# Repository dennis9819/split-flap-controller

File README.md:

# 3D Printable split flap display

Welcome to **split-flap-controller**, the firmware + hardware design for driving a modular, scalable split-flap display system.

Development of this project began in 2024 with the goal of creating a robust, DIY split-flap display that anyone can build and customize themselves. Inspired by the iconic Frankfurt Airport display, this project aims to recreate the nostalgic mechanical aesthetic and characteristic flipping sound that made those displays so memorable.

__Ongoing Project! This repository is not final.__

## Project goals
- **Modularity** – Each flap module is independent and addressable, allowing for scalable display sizes.  
- **DIY-Friendly Design** – Open schematics, PCBs, and firmware make it accessible for makers and hobbyists.  
- **Robust Firmware** – Written in C, with features like error handling, EEPROM-stored calibration, and motor homing logic.  
- **Authentic Aesthetic** – Recreates the distinctive motion and sound of traditional airport-style displays.  
- **Modern Communication** – Supports RS-485 half-duplex at 57600 baud with WebSocket integration for control from a host system.  
- **Open for Extension** – Designed to support other MCUs, motor drivers, or mechanical formats.

## Features

### Hardware
- SMD-based controller board (Atmega8 MCU)  
- Modular RS-485 communication chain 
- Integrated motor driver and position sensor handling
- Modules connect to a single backplane
- Hall-effect sensor homing
- Robust error handling
  - detects homing faults, stuck drums, overcurrent and bus errors
  - activates a failSafe condition on critical fault
  - can be reset via RS485 in most conditions
  - checks validity of each packet via checksum

### Firmware
- Lightweight communication protocol with checksum and addressing  
- Fault detection (homing failure, overcurrent, invalid position)  
- Persistent settings stored in EEPROM  
- CRC check of each message

### Software
- WebSocket-based control server  
- Modular architecture for future GUI or API integrations  
- Easily portable to other platforms and MCUs
- Nginx Webserver allows you to controll the display with your smartphone
- very fast and written in plan c. I'm using libjson and libws for JSON handling and the WebSocket server

## CAD
This display is designed in **Fusion360**. All schematics and boards are designed in **KiCAD 9**.

Most parts can be 3d printed. The modular backpanel needs to be fabricated from sheetmetal. You can use suppliers like JLCPCB for manufacturing or design a different 3d printable solution.

If you want to generate custom flaps, you can find my flap generator here: [split-flap-generator](https://github.com/dennis9819/split-flap-generator)

## License

This project is open source and available under the [AGPL-3.0 License](LICENSE).

## Documentation
- [SFBus Protocol](software/pc_client/doc/sfbus-proto.md)
- [Websockets Protocol](software/pc_client/doc/api-doc.md)
- [BOM](cad/BOM_FlapUnit.md)
- Build guide wil follow soon!

## Power Consumption
Each Module pulls arround 110mA. This is roughly 1.4W of power. 
This can be reduced by turning off the motors in idle. 

---
## Credits
This is a 3D printable, expandable split flap display based on the original design of [David Königsmann](https://github.com/davidkingsman/split-flap).
This version uses his drum and flap design but completly redesigns the rest of the system.

The firmware as well as the Server is completly rewritten from scratch.

Feel free to checkout his more affordable and diy friendly design.

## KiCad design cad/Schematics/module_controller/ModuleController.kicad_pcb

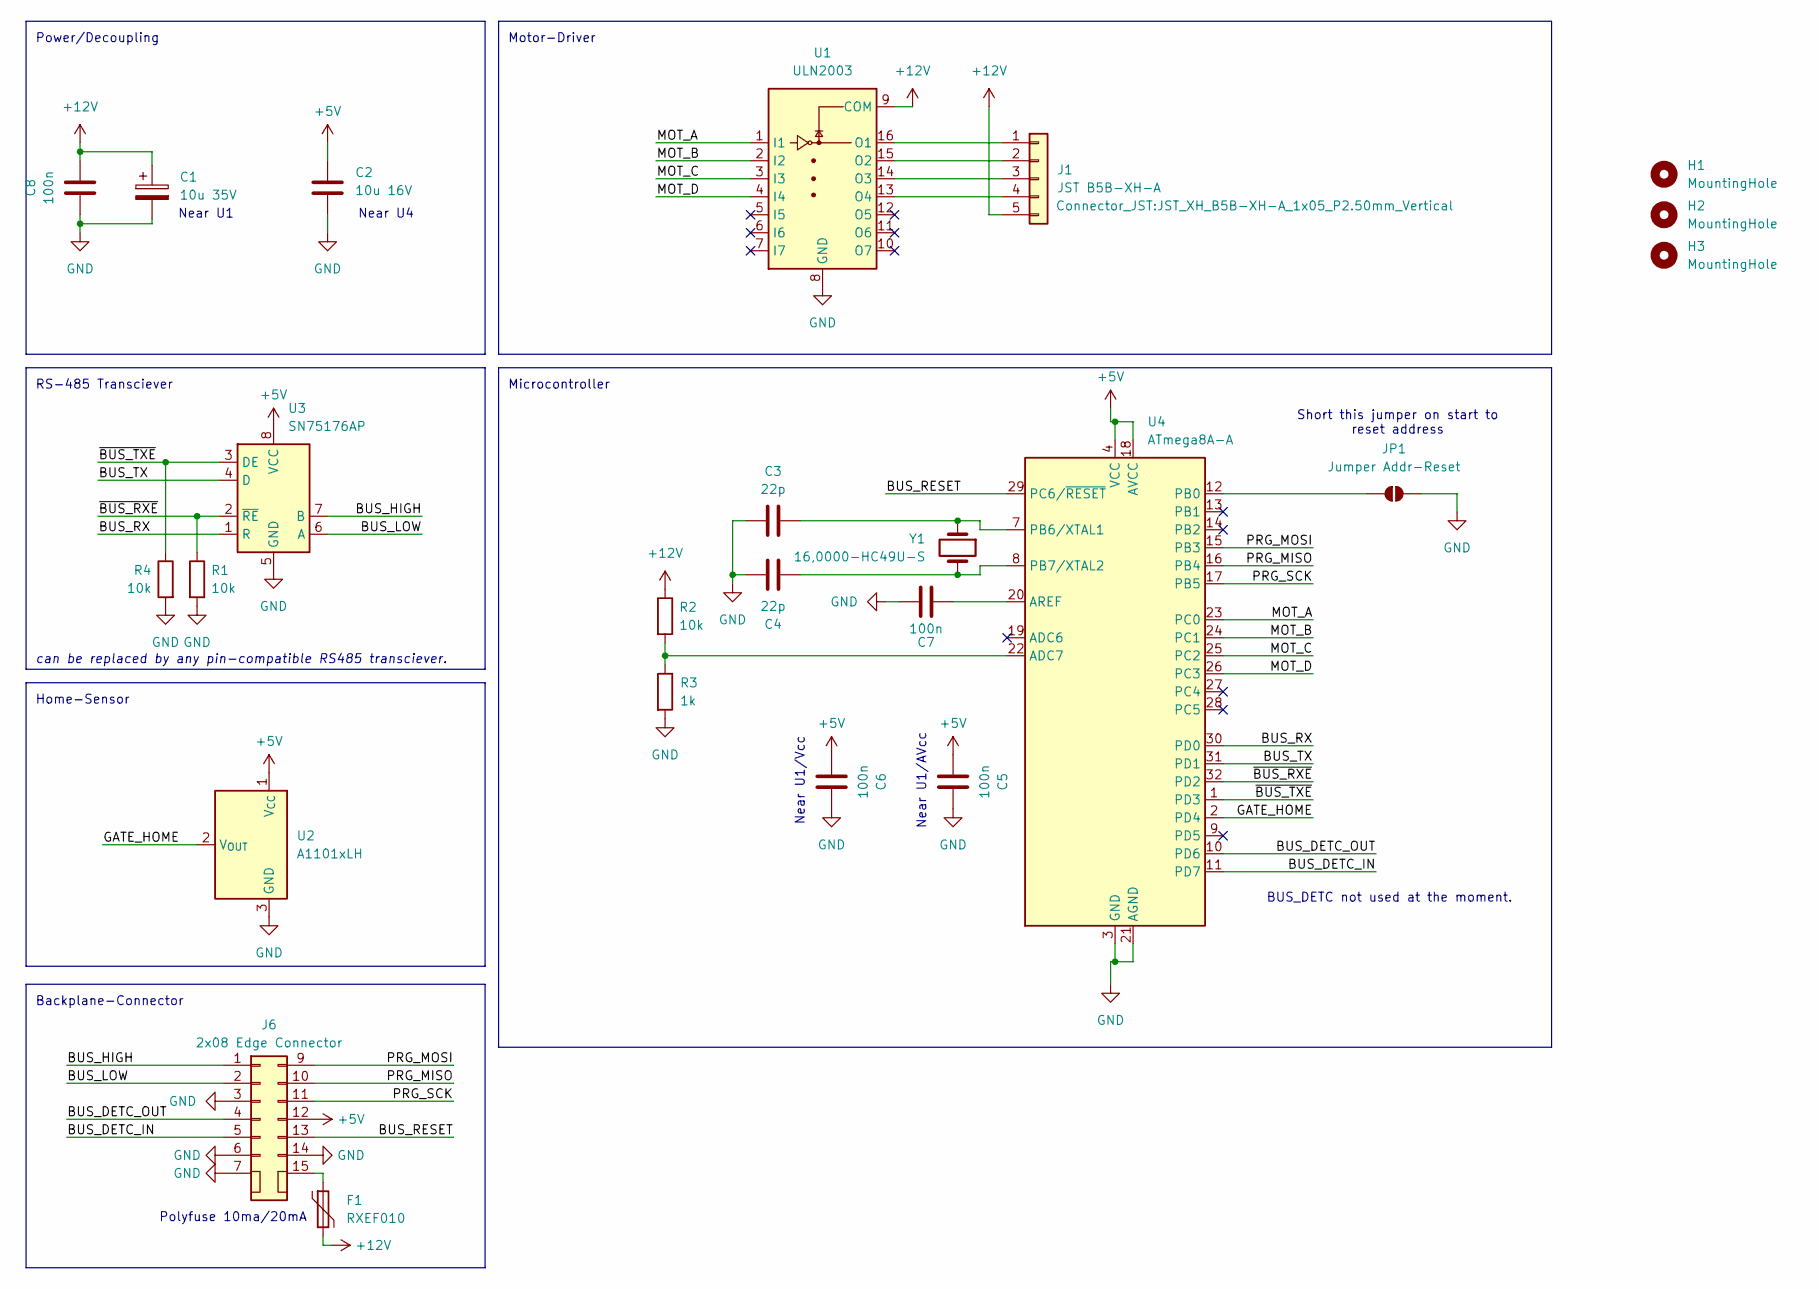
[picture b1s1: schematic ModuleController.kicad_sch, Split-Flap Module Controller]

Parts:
C1: 10u 35V; CP_Radial_D6.3mm_P2.50mm
C2: 10u 16V; C_1206_3216Metric
C3, C4: 22p; C_0805_2012Metric
C5, C6, C7, C8: 100n; C_0805_2012Metric
F1: RXEF010; Fuse_0805_2012Metric
H1, H2, H3: MountingHole; MountingHole_3.2mm_M3_DIN965_Pad
J1: JST B5B-XH-A; JST_XH_B5B-XH-A_1x05_P2.50mm_Vertical
J6: 2x08 Edge Connector; Card Edge 16 power
JP1: Jumper Addr-Reset; SolderJumper-2_P1.3mm_Open_Pad1.0x1.5mm
R1, R2, R4: 10k; R_0805_2012Metric
R3: 1k; R_0805_2012Metric
U1: ULN2003; DIP-16_W7.62mm
U2: A1101xLH; SOT-23W
U3: SN75176AP; DIP-8_W7.62mm
U4: ATmega8A-A; TQFP-32_7x7mm_P0.8mm
Y1: 16,0000-HC49U-S; Crystal_HC49-U_Vertical

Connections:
+5V: C2.1, C5.2, C6.2, J6.12, U2.1 (V_{CC}), U3.8 (VCC), U4.4 (VCC), U4.6 (VCC), U4.18 (AVCC)
+12V: C1.1, C8.1, F1.2, J1.5, R2.1, U1.9 (COM)
/BUS_DETC_IN: J6.5, U4.11 (PD7)
/BUS_DETC_OUT: J6.4, U4.10 (PD6)
/BUS_HIGH: J6.1, U3.7 (B)
/BUS_LOW: J6.2, U3.6 (A)
/BUS_RESET: J6.13, U4.29 (PC6/~RESET)
/BUS_RX: U3.1 (R), U4.30 (PD0)
/BUS_TX: U3.4 (D), U4.31 (PD1)
/GATE_HOME: U2.2 (V_{OUT}), U4.2 (PD4)
/MOT_A: U1.1 (I1), U4.23 (PC0)
/MOT_B: U1.2 (I2), U4.24 (PC1)
/MOT_C: U1.3 (I3), U4.25 (PC2)
/MOT_D: U1.4 (I4), U4.26 (PC3)
/PRG_MISO: J6.10, U4.16 (PB4)
/PRG_MOSI: J6.9, U4.15 (PB3)
/PRG_SCK: J6.11, U4.17 (PB5)
/~BUS_RXE: R1.1, U3.2 (~RE), U4.32 (PD2)
/~BUS_TXE: R4.1, U3.3 (DE), U4.1 (PD3)
GND: C1.2, C2.2, C3.1, C4.1, C5.1, C6.1, C7.1, C8.2, J6.3, J6.6, J6.7, J6.14, JP1.2 (B), R1.2, R3.2, R4.2, U1.8 (GND), U2.3 (GND), U3.5 (GND), U4.3 (GND), U4.5 (GND), U4.21 (AGND)
unnamed: J1.1, U1.16 (O1)
unnamed: J1.2, U1.15 (O2)
unnamed: J1.3, U1.14 (O3)
unnamed: J1.4, U1.13 (O4)
unnamed: F1.1, J6.15
unnamed: JP1.1 (A), U4.12 (PB0)
unnamed: R2.2, R3.1, U4.22 (ADC7)
unnamed: C7.2, U4.20 (AREF)
unnamed: C3.2, U4.7 (PB6/XTAL1), Y1.1
unnamed: C4.2, U4.8 (PB7/XTAL2), Y1.2

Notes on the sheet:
Motor-Driver
RS-485 Transciever
Power/Decoupling
Polyfuse 10ma/20mA
Home-Sensor
Short this jumper on start to reset address
Backplane-Connector
BUS_DETC not used at the moment.
Near U1
can be replaced by any pin-compatible RS485 transciever.
Near U1/AVcc
Near U1/Vcc
Microcontroller
Near U4

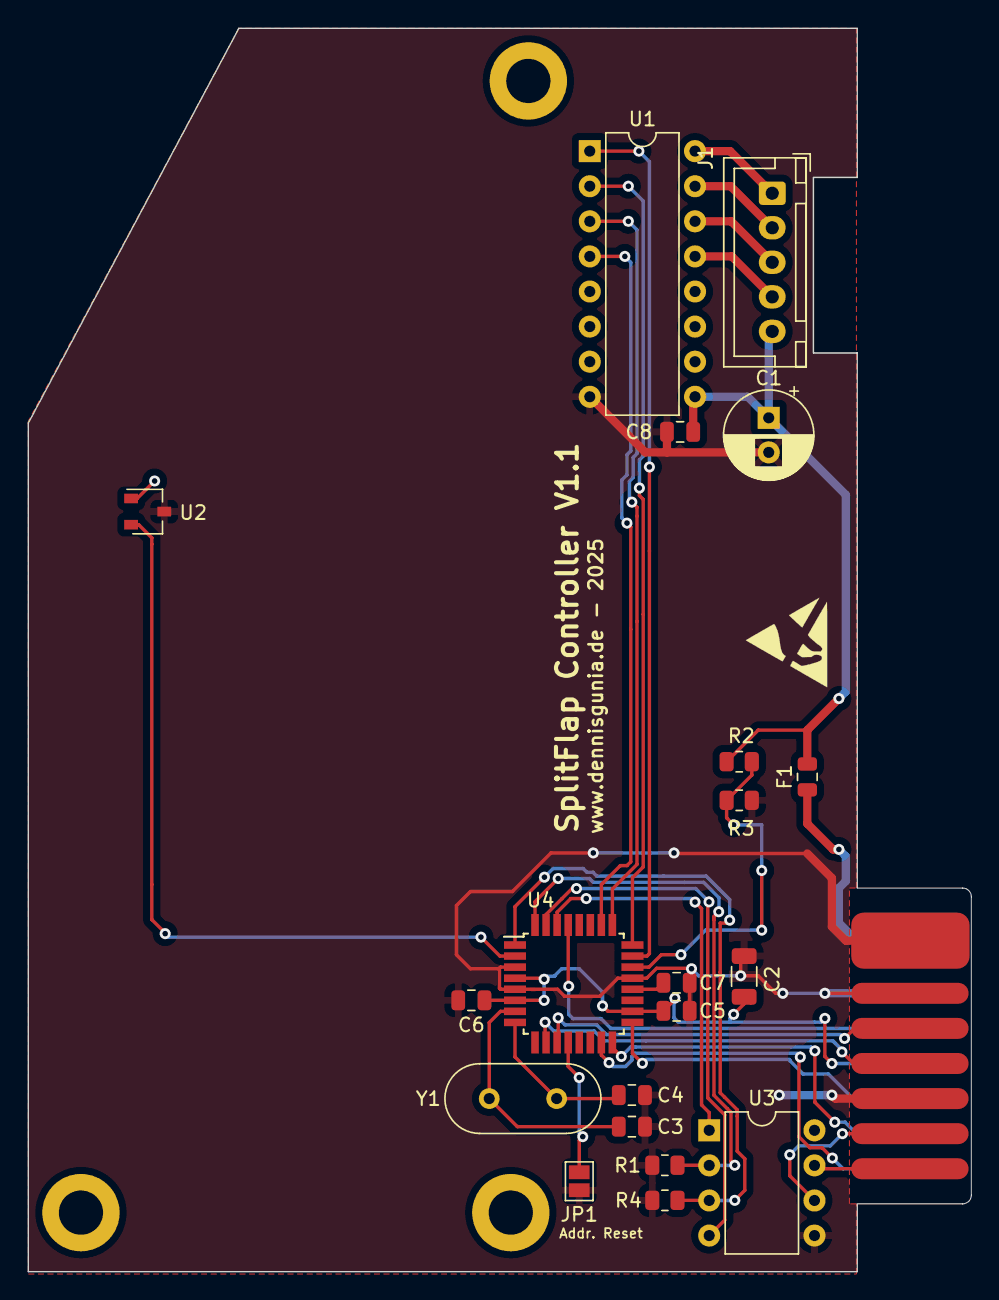
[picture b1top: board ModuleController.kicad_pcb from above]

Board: 2 copper layers, 68.3 x 90.0 mm, 24 parts (0 on the bottom side), 30 nets.

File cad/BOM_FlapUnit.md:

# Bill of Material for 1U/2U Flap Unit

## 3D Printed Parts 
| part-number | part | file | amount | notes |
| ----------- | ---- | ---- | ------ | ----- |
| FU-001 | Unit Frame Base     | STL Unit/splitflap-unit-base.stl | 1 | common for all units |
| FU-002 | Unit Frame Cover 1U | STL Unit/splitflap-cover-1u.stl  | 1 | only for 1U wide unit|
| FU-003 | Unit Frame Cover 2U | STL Unit/splitflap-cover-2u.stl  | 1 | only for 2U wide unit|
| FU-004 | Unit Drum Core      | STL Unit/splitflap-drum-core.stl | 1 | common for all units |
| FU-005 | Unit Drum Core 1U   | STL Unit/splitflap-drum-outer-1u.stl | 1 | only for 1U wide unit|
| FU-006 | Unit Drum Core 2U   | STL Unit/splitflap-drum-outer-2u.stl | 1 | only for 2U wide unit|
| FU-007 | Flaps   | ... | 45 | |
- 49 Individual Parts per module

## Hardware

| part-number | part | amount | notes |
| ----------- | ---- | ------ | ----- |
| FU-011      | Ball Bearing 684ZZ (9 x 4 x 4mm) | 1 | |
| FU-012      | Stepper 28BYJ-48 DC 12V | 1 |  **!! Use 12V Variant. NOT 5V !!**|
| FU-013      | Heat insert M3 x 3mm | 3 | |
| FU-014      | Heat insert M3 x 5mm | 4 | |
| FU-015      | M3x5 Screw DIN 912 | 3 | |
| FU-016      | M3x12 Screw DIN 912 | 2 | |
| FU-017      | M3x8 Screw DIN EN ISO 10642 | 2 | |
| FU-018      | Magnet round d=2mm | 1 | |
- 17 Individual Parts per module

## Electronics
| part-number | part | amount | notes |
| ----------- | ---- | ------ | ----- |
| FU-031      | Module Controller PCB | 1 | |
| FU-032      | ATmega8A-A | 1 | |
| FU-033      | SN75176AP | 1 | |
| FU-034      | ULN2003 | 1 | Can be salvaged from the driver board that usually comes with the stepper motor |
| FU-035      | A1101xLH | 1 | SOT-23W variant! |
| FU-036      | 16,0000-HC49U-S Crystal | 1 |  |
| FU-037      | Capacitor 10u 35V (Radial_D6.3mm_P2.50mm) | 1 |  |
| FU-038      | Capacitor 10u 16V (1206) | 1 |  |
| FU-039      | Capacitor 22p (0805) | 2 |  |
| FU-040      | Capacitor 100n (0805) | 4 |  |
| FU-041      | Fuse 200mA (0805) | 1 |  |
| FU-042      | JST B5B-XH-A | 1 |  |
| FU-043      | Resistor 1k | 1 |  |
| FU-044      | Resistor 10k | 3 |  |
- 20 Individual Parts per module


## Summary:
Parts per module: 76 (mostly 3d printed)

# Bill of Material for 4Unit Backplane

## 3D Printed Parts 
| part-number | part | file | amount | notes |
| ----------- | ---- | ---- | ------ | ----- |
| FP-001      | Upper Slot | STL Slot/splitflap-slot-upper.stl | 1 |  |
| FP-002      | Lower Slot | STL Slot/splitflap-slot-lower.stl | 1 |  |
- 2 Individual Parts per module

## Sheet metal
| part-number | part | file | amount | notes |
| ----------- | ---- | ---- | ------ | ----- |
| FP-003      | Backplane | Sheet Metal/sheet-metal-backplate.dxf | 1 |  |
- 1 Individual Parts per module

## Hardware
| part-number | part | amount | notes |
| ----------- | ---- | ------ | ----- |
| FP-011      | Heat insert M4 x 5mm | 4 | |
| FP-012      | Heat insert M3 x 5mm | 4 | |
| FP-013      | M3x5 Screw DIN 912 | 8 | |
| FP-014      | M4x10 Screw DIN 912 | 4 | |
| FP-015      | M3x5 Standoff | 8 | |
| FP-016      | M3 Nut | 4 | |
- 32 Individual Parts per module

## Electronics
| part-number | part | amount | notes |
| ----------- | ---- | ------ | ----- |
| FU-031      | Backplane PCB | 1 | |
| FU-032      | PhoenixContact_MSTBA_2,5_2-G-5,08 | 2 | |
| FU-033      | Phoenix_MSTB:PhoenixContact_MSTBA_2,5_3-G-5,08 | 4 | |
| FU-034      | L7805 | 1 |  |
| FU-035      | 74AHCT1G125 | 1 | |
| FU-036      | 2x08 Edge Connector | 4 |  |
- 13 Individual Parts per module

## Summary:
Parts per assembly: 48 

# Bill of Material for Backplane connection bracket
## Sheet metal
| part-number | part | file | amount | notes |
| ----------- | ---- | ---- | ------ | ----- |
| FC-001      | Bracket | sheet-metal-connector-middle.dxf | 1 |  |
- 1 Individual Parts per module

## Hardware
| part-number | part | amount | notes |
| ----------- | ---- | ------ | ----- |
| FC-011      | M4x10 | 8 | |
| FC-012      | M4 Nut | 8 | |
- 16 Individual Parts per module

## Summary:
Parts per assembly: 17 

# Parts for full display (12x3)
- Display Units: 36 (2736 Parts)
- Backplane Units: 9 (432 Parts)
- Backplane Connectors: 12 (204 Parts)
- Sum: 3372 Individual Parts

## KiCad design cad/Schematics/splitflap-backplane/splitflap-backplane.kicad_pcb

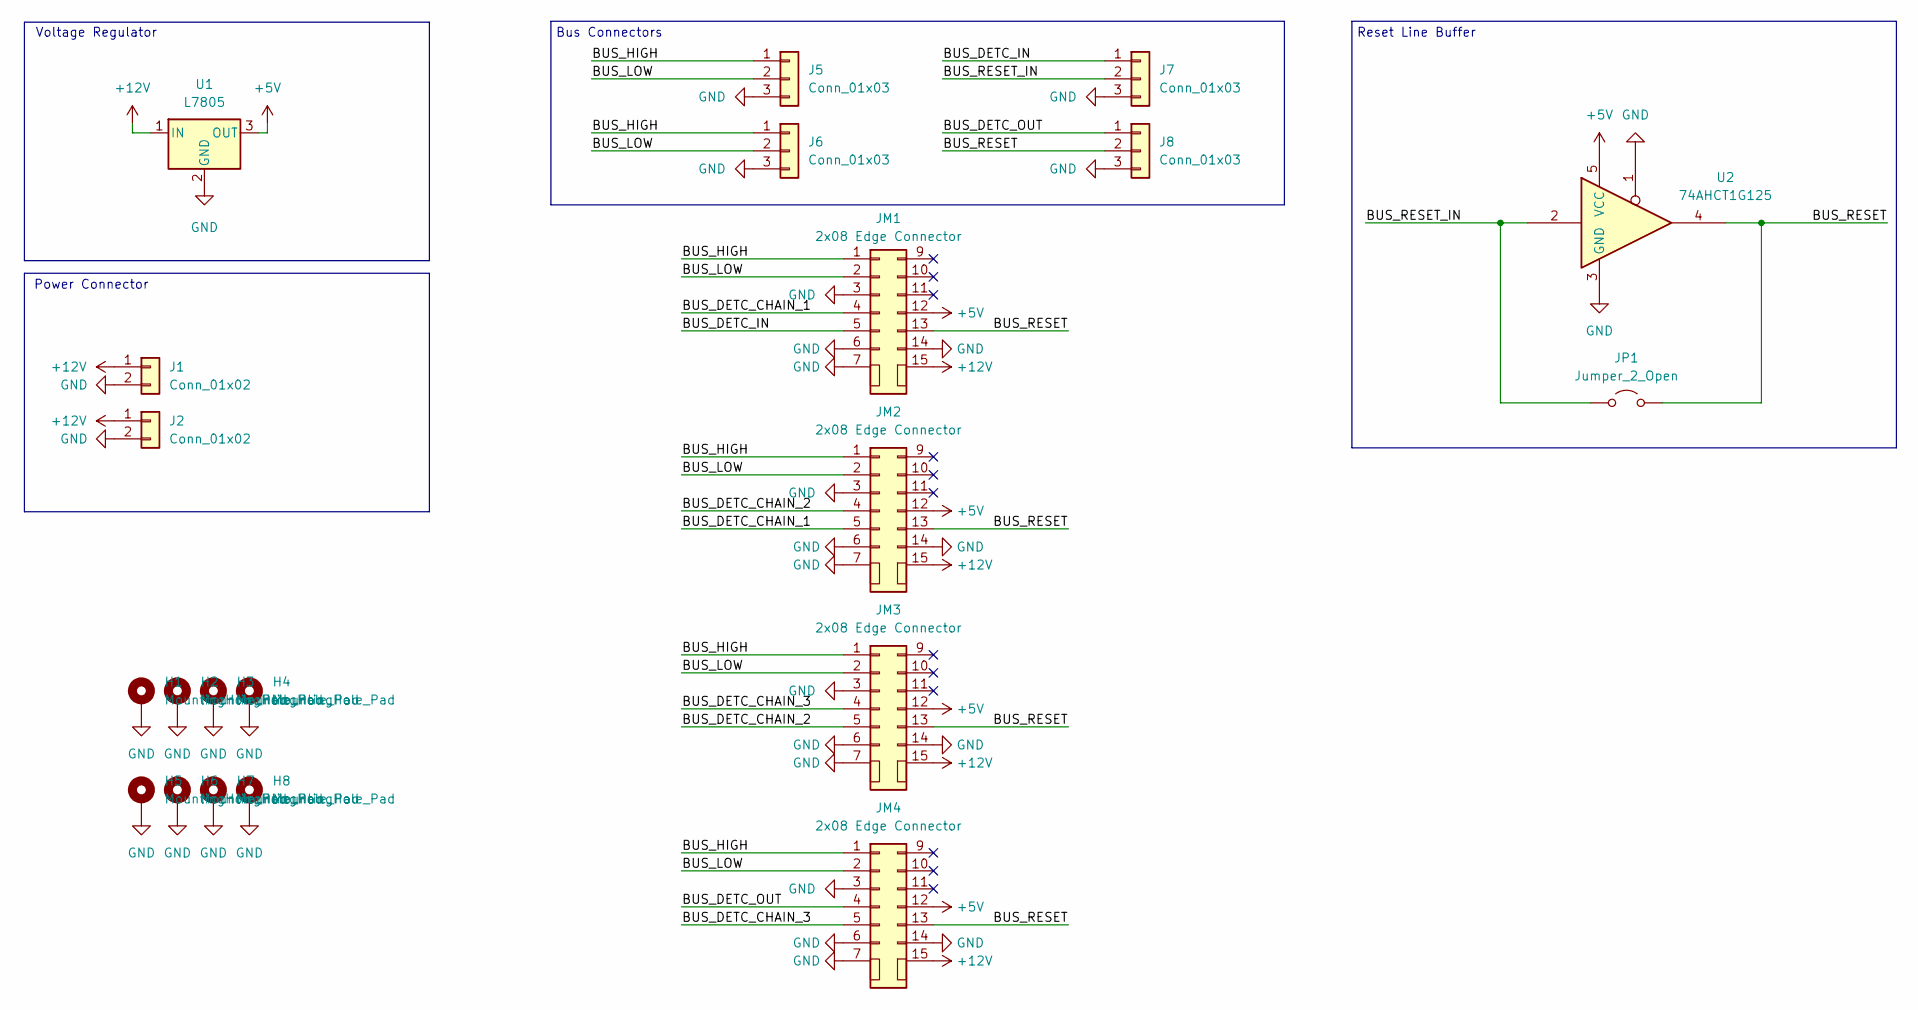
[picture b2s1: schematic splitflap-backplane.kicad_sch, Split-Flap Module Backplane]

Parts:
H1, H2, H3, H4, H5, H6, H7, H8: MountingHole_Pad; MountingHole_2.7mm_M2.5_DIN965_Pad
J1, J2: Conn_01x02; PhoenixContact_MSTBA_2,5_2-G-5,08_1x02_P5.08mm_Horizontal
J5, J6, J7, J8: Conn_01x03; PhoenixContact_MSTBA_2,5_3-G-5,08_1x03_P5.08mm_Horizontal
JM1, JM2, JM3, JM4: 2x08 Edge Connector; Card-Socket Flap Module
JP1: Jumper_2_Open; SolderJumper-2_P1.3mm_Open_Pad1.0x1.5mm
U1: L7805; TO-220-3_Horizontal_TabDown
U2: 74AHCT1G125; SOT-353_SC-70-5

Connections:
+5V: JM1.12, JM2.12, JM3.12, JM4.12, U1.3 (OUT), U2.5 (VCC)
+12V: J1.1, J2.1, JM1.15, JM2.15, JM3.15, JM4.15, U1.1 (IN)
/BUS_DETC_CHAIN_1: JM1.4, JM2.5
/BUS_DETC_CHAIN_2: JM2.4, JM3.5
/BUS_DETC_CHAIN_3: JM3.4, JM4.5
/BUS_DETC_IN: J7.1, JM1.5
/BUS_DETC_OUT: J8.1, JM4.4
/BUS_HIGH: J5.1, J6.1, JM1.1, JM2.1, JM3.1, JM4.1
/BUS_LOW: J5.2, J6.2, JM1.2, JM2.2, JM3.2, JM4.2
/BUS_RESET: J8.2, JM1.13, JM2.13, JM3.13, JM4.13, JP1.2 (B), U2.4
/BUS_RESET_IN: J7.2, JP1.1 (A), U2.2
GND: H1.1, H2.1, H3.1, H4.1, H5.1, H6.1, H7.1, H8.1, J1.2, J2.2, J5.3, J6.3, J7.3, J8.3, JM1.3, JM1.6, JM1.7, JM1.14, JM2.3, JM2.6, JM2.7, JM2.14, JM3.3, JM3.6, JM3.7, JM3.14, JM4.3, JM4.6, JM4.7, JM4.14, U1.2 (GND), U2.1, U2.3 (GND)

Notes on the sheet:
Voltage Regulator
Reset Line Buffer
Power Connector
Bus Connectors

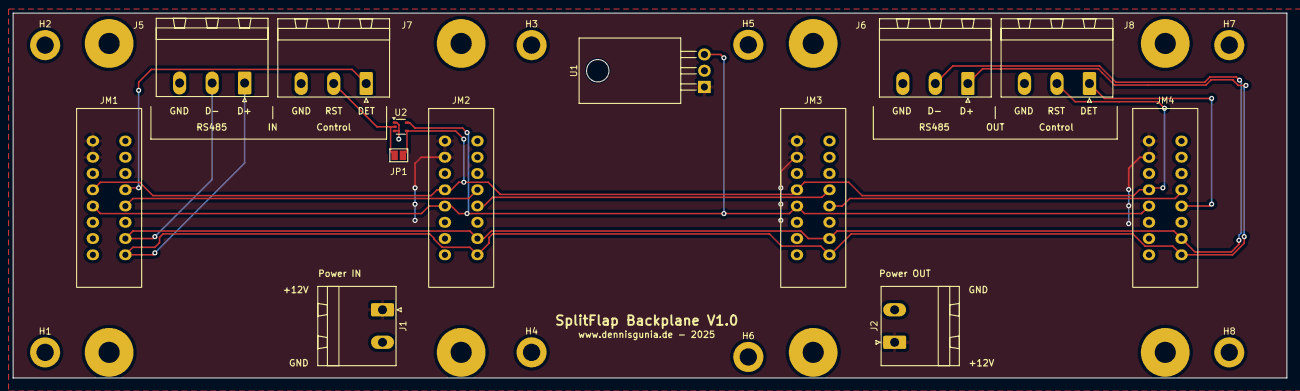
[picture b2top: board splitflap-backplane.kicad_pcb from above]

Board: 2 copper layers, 199.0 x 57.0 mm, 21 parts (0 on the bottom side), 12 nets.

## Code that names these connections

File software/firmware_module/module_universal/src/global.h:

/* Copyright (C) 2025 Dennis Gunia - All Rights Reserved
 * You may use, distribute and modify this code under the
 * terms of the  AGPL-3.0 license.
 *
 * https://www.dennisgunia.de
 * https://github.com/dennis9819/splitflap_v1
 */

#include <avr/interrupt.h>
#include <avr/io.h>
#include <avr/iom8.h>
#include <avr/wdt.h>
#include <stdlib.h>
#include <string.h>
#include <util/delay.h>


// I/O Pin definition
#define BUX_RX PD0      // RX Pin (to buffer)
#define BUX_TX PD1      // TX Pin (to buffer)
#define BUX_DIR PD2     // Buffer direction pin
#define SENSOR_HOME PD3 // Home sensor pin

#define MOTOR_A PC0 // Motor phase A driver
#define MOTOR_B PC1 // Motor phase B driver
#define MOTOR_C PC2 // Motor phase C driver
#define MOTOR_D PC3 // Motor phase D driver

// EEPROM Addresses
#define CONF_CONST_OKAY (uint8_t)0xAA
#define CONF_ADDR_OKAY 0x0004
#define CONF_ADDR_ADDR 0x0000
#define CONF_ADDR_OFFSET 0x0002

// Protocol definitions
#define PROTO_MAXPKGLEN 64 // maximum size of package in bytes

// Command Bytes
#define CMDB_SETVAL (uint8_t)0x10  // Set display value
#define CMDB_SETVALR (uint8_t)0x11 // Set display value and do a full rotation
#define CMDB_EEPROMR (uint8_t)0xF0 // Read EEPROM
#define CMDB_EEPROMW (uint8_t)0xF1 // Write EEPROM
#define CMDB_GSTS (uint8_t)0xF8    // Get status
#define CMDB_PING (uint8_t)0xFE    // Ping
#define CMDB_RESET (uint8_t)0x30   // Reset device
#define CMDB_PWRON (uint8_t)0x21   // Power motor on
#define CMDB_RPWROFF (uint8_t)0x20 // Power motor off
#define CMDB_GVER (uint8_t)0xF9    // Get Firmware Version

// Command Responses
#define CMDR_ERR_INVALID 0xEE // Invalid command
#define CMDR_ACK 0xAA         // Acknowledge
#define CMDR_PING 0xFF        // Ping response

// Utility definitions
#define SHIFT_0B 0
#define SHIFT_1B 8
#define SHIFT_2B 16
#define SHIFT_3B 24

// Firmware Version
#define FVER_SEMVER_MINOR 1
#define FVER_SEMVER_PATCH 0

// Hardware Config
#if BOARD_REV == 1

#define PIN_SENSE PD3
#define PIN_RS485_TXE PD2
#define PIN_RS485_RXE PD2
#define FVER_SEMVER_MAJOR 1
#define MOTOR_DIR 0


#elif BOARD_REV == 2

#define PIN_SENSE PD4
#define PIN_RS485_TXE PD2
#define PIN_RS485_RXE PD3
#define FVER_SEMVER_MAJOR 2
#define MOTOR_DIR 1

#else

#define PIN_SENSE PD3
#define PIN_RS485_TXE PD2
#define PIN_RS485_RXE PD2
#define FVER_SEMVER_MAJOR 0
#define MOTOR_DIR 0
#warning "BOARD_REV not specified!"

#endif

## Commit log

2025-01-09 Create LICENSE
2025-01-09 Added intital Readme
2025-01-10 Added fuse settings to makefile
2025-01-10 refactor v1
2025-01-10 added kicad generation script
2025-01-10 Refactor schematics
2025-01-10 Add licence
2025-02-21 improved formatting and fixed clangd includes
2025-02-21 removed example sketch
2025-02-21 fix clangd and comments
2025-09-11 update schematics
2025-09-11 improve readability
2025-09-11 cleanup
2025-09-12 fix controller for ftdi485
2025-09-12 fix calibration
2025-09-18 added webserver
2025-09-18 add wsserver to makefile
2025-09-18 updated schematics
2025-09-18 updated documentation
2025-09-18 add licence to source code + add protocol v2
2025-09-18 add documentation
2025-09-18 fix typo
2025-10-08 add protocol version2
2025-10-10 refactor, add cad
2025-10-12 add 3d view
2025-10-12 Add BOM
2025-10-12 Fix BOM
2025-10-19 fix protocol V2 bug
2025-10-19 add web ui
2025-10-19 fix stl files
2025-10-19 add power section to doc
2025-10-19 added logger
2025-10-19 reorganize code and added documentation
2025-10-19 add logger docs
2025-10-19 add copyright details to webserver
2025-10-20 fix bugs
2025-10-20 add color to log output
2025-10-20 added additional error handling
2025-10-20 fix includes and type
2025-10-21 fix segfault on load
2025-10-22 added firmware for new pcb revision
2025-10-22 add flash feature to makefile
2025-10-22 add notifications and better url handling
2025-10-22 patch voltage readout for new firmware version
2025-10-22 add boradcast base and fix oob error on invalid flap char
2025-11-01 fix sense pin
2025-11-01 add functions to makefile
2025-11-01 fix address form and calibration form
2025-11-01 add print profiles and update schematics
2025-11-01 update gitignore
2025-11-02 combine module firmware revisions into single project. Expand makefile
2025-11-02 fix error message
2025-11-02 remove build files
2025-11-02 fix print profile
2025-11-02 update schematics annotation
2025-11-02 remove eeprom temp file
2025-11-02 changed firmware version
2025-11-02 Add graphics
2025-11-02 fix motor standby and overheating issue
2026-01-01 fixed buffer overflow in processing function and added documentation
2026-01-01 added firmware readout and enhance makefile
2026-01-01 add demo program
2026-01-01 update settings
2026-01-01 Add history and recall options for web gui
2026-01-01 add dockerfile
2026-01-01 fix documentation
2026-01-02 added sync mode
2026-01-02 expand web gui
2026-01-02 web ui styling and logo
